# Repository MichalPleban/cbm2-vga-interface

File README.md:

# VGA interface for Commodore CBM-II computers

This project adds a VGA interface to Commodore CBM-II machines. The board can be installed in both low-profile and high-profile machines and adds a VGA connector which mirrors the main display.

## Project aims

This is a VGA **interface**, not a VGA **graphics card**. It does not add any graphical capabilities to your computer besides those it already possesses. What it does is to allow you to connect your computer to a modern VGA display (or a VGA-to-HDMI converter), giving you a better quality picture than a composite video output.

Due to the nature of its operation (explained below), it will also allow you to check the operation of your computer if you don't get any display from it. Since it does not depend on the inbuilt video circuitry, you can check if the CPU is booting even if the primary display is not working.

## Project status

The hardware part is ready. You can find the PCB files from the `eagle` directory. There are two PCBs: main board (to be installed in an expansion socket on the mainboard) and connector board (to be installed, for example, on the metal backplate). The boards are connected via a 2x5 pin header cable (for example, a JTAG cable).

The firmware is not yet completed but it is usable enough. It displays the picture, allows for cursor positioning and switching between text and graphics mode. These features are enough to use your computer. Advanced CRTC functions (such as changing the cursor shape) are not yet supported. You can find the current firmware binary in the `firmware` directory. You need to program the onboard 24C256 EEPROM chip with the firmware.

## How it works?

The board is centered around a Propeller v1 chip which generates a 640x480 VGA video signal. The chip is programmed to silently sniff signals on the 6509 CPU bus and react to writes to the I/O area. Through this it maintains its own copy of the video memory as well as the CRTC and TPI registers, which allows it to re-create the screen contents and display it on the VGA connector.

This way the board does not need any changes in the KERNAL video routines. Also, since it doesn't use the original video signal in ay way, you can use the board even if the primary video circuitry of the computer is not working.

## Advanced stuff

The board is also meant to be used with the 8088 board. To that end it provides a second display mode which is compatible with IBM MDA display. This mode uses an IBM 8x16 font and recognizes all MDA attributes (bright, invert, underline, blink).

There is a second connector on the board labeled `INPUT`. It is meant for daisy-chaining a secondary video board [when it is developed :)]. When a secondary board is connected, the video outputs of the primary board are tristated. This way the two cards can share the same VGA output connector.

The Propeller emits a 50 Hz signal on one of the pins. This signal is very useful if you want to replace the original power supply with a modern one. Besides various voltages, the original PSU supplies a 50 Hz signal, which modern PSUs do not. You can now easily overcome this problem by shorting the JP2 jumper on the VGA interface which will then provide the needed 50 Hz signal to the mainboard.

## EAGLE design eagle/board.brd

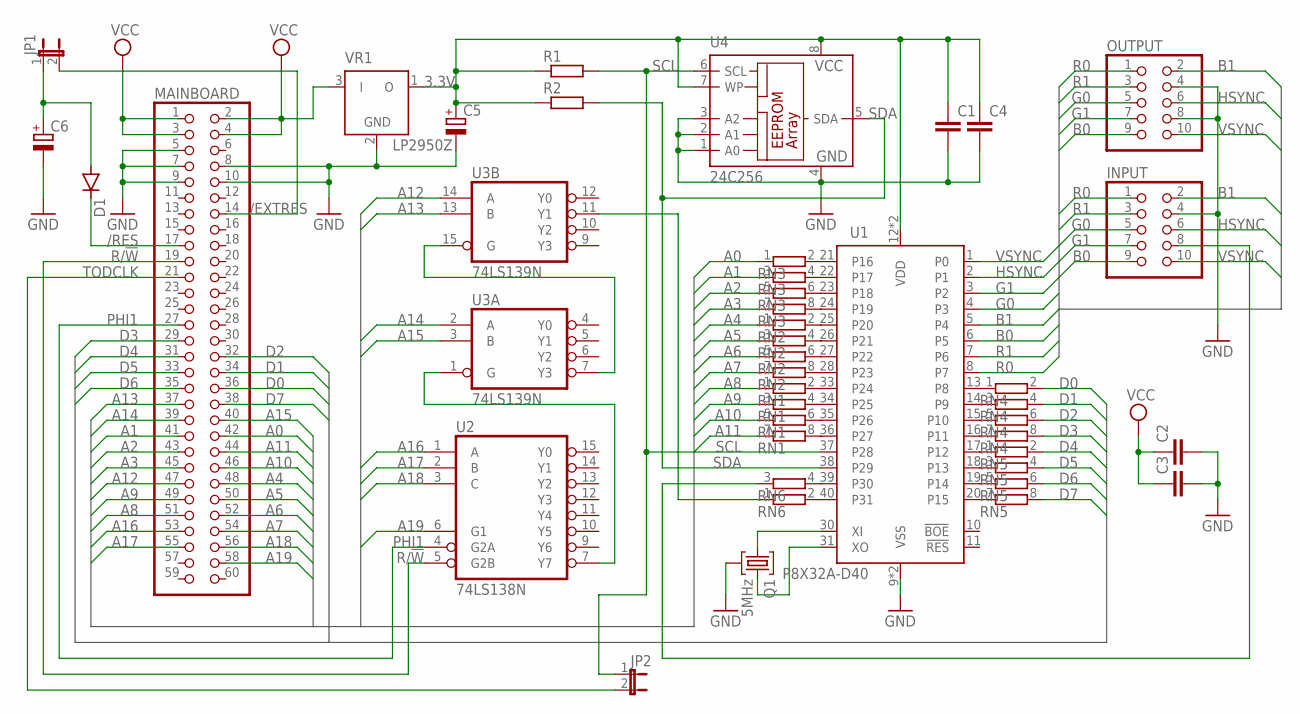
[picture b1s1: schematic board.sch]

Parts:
C1, C2, C3, C4: C2.5/2; C2.5-2
C5, C6: CPOL-EUE5-6; E5-6
D1: 1N4148DO35-7; DO35-7
INPUT: PINHD-2X5; 2X05
JP1, JP2: JP1E; JP1
MAINBOARD: PINHD-2X30; 2X30
OUTPUT: PINHD-2X5; 2X05
Q1: 5MHz; UM1
R1, R2: R-EU_0204/7; 0204/7
RN1, RN2, RN3, RN4, RN5, RN6: E4RP; SIL8
U1: P8X32A-D40; DIL40
U2: 74LS138N; DIL16
U3: 74LS139N; DIL16
U4: 24C256; DIL8
VR1: LP2950Z; TO92

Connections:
3.3V: C1.1, C4.1, C5.+, R1.1, R2.1, U1.12 (VDD), U1.32 (VDD), U4.7 (WP), U4.8 (VCC), VR1.1 (O)
/EXTRES: JP1.2, MAINBOARD.14
/RES: D1.C, MAINBOARD.17
A0: MAINBOARD.42, RN3.1
A1: MAINBOARD.41, RN3.3 (1)
A2: MAINBOARD.43, RN3.5 (1)
A3: MAINBOARD.45, RN3.7 (1)
A4: MAINBOARD.48, RN2.1
A5: MAINBOARD.50, RN2.3 (1)
A6: MAINBOARD.52, RN2.5 (1)
A7: MAINBOARD.54, RN2.7 (1)
A8: MAINBOARD.51, RN1.1
A9: MAINBOARD.49, RN1.3 (1)
A10: MAINBOARD.46, RN1.5 (1)
A11: MAINBOARD.44, RN1.7 (1)
A12: MAINBOARD.47, U3.14 (A)
A13: MAINBOARD.37, U3.13 (B)
A14: MAINBOARD.39, U3.2 (A)
A15: MAINBOARD.40, U3.3 (B)
A16: MAINBOARD.53, U2.1 (A)
A17: MAINBOARD.55, U2.2 (B)
A18: MAINBOARD.56, U2.3 (C)
A19: MAINBOARD.58, U2.6 (G1)
B0: INPUT.9, OUTPUT.9, U1.6 (P5)
B1: INPUT.2, OUTPUT.2, U1.5 (P4)
D0: MAINBOARD.36, RN4.2
D1: MAINBOARD.34, RN4.4 (2)
D2: MAINBOARD.32, RN4.6 (2)
D3: MAINBOARD.29, RN4.8 (2)
D4: MAINBOARD.31, RN5.2
D5: MAINBOARD.33, RN5.4 (2)
D6: MAINBOARD.35, RN5.6 (2)
D7: MAINBOARD.38, RN5.8 (2)
G0: INPUT.5, OUTPUT.5, U1.4 (P3)
G1: INPUT.7, OUTPUT.7, U1.3 (P2)
GND: C1.2, C2.2, C3.2, C4.2, C5.-, C6.-, INPUT.4, MAINBOARD.5, MAINBOARD.7, MAINBOARD.8, MAINBOARD.9, MAINBOARD.10, OUTPUT.4, OUTPUT.8, Q1.2, U1.9 (VSS), U1.29 (VSS), U2.8 (GND), U3.8 (GND), U4.1 (A0), U4.2 (A1), U4.3 (A2), U4.4 (GND), VR1.2 (GND)
HSYNC: INPUT.6, OUTPUT.6, U1.2 (P1)
unnamed: U2.7 (Y7), U3.1 (G)
unnamed: U3.7 (Y3), U3.15 (G)
unnamed: RN6.1, U3.11 (Y1)
unnamed: RN1.8 (2), U1.36 (P27)
unnamed: RN1.6 (2), U1.35 (P26)
unnamed: RN1.4 (2), U1.34 (P25)
unnamed: RN1.2, U1.33 (P24)
unnamed: RN2.8 (2), U1.28 (P23)
unnamed: RN2.6 (2), U1.27 (P22)
unnamed: RN2.4 (2), U1.26 (P21)
unnamed: RN2.2, U1.25 (P20)
unnamed: RN3.8 (2), U1.24 (P19)
unnamed: RN3.6 (2), U1.23 (P18)
unnamed: RN3.4 (2), U1.22 (P17)
unnamed: RN3.2, U1.21 (P16)
unnamed: RN5.7 (1), U1.20 (P15)
unnamed: RN5.5 (1), U1.19 (P14)
unnamed: RN5.3 (1), U1.18 (P13)
unnamed: RN5.1, U1.17 (P12)
unnamed: RN4.7 (1), U1.16 (P11)
unnamed: RN4.5 (1), U1.15 (P10)
unnamed: RN4.3 (1), U1.14 (P9)
unnamed: RN4.1, U1.13 (P8)
unnamed: RN6.2, U1.40 (P31)
unnamed: RN6.4 (2), U1.39 (P30)
unnamed: Q1.1, U1.30 (XI)
unnamed: Q1.3, U1.31 (XO)
unnamed: C6.+, D1.A, JP1.1
unnamed: INPUT.8, RN6.3 (1)
PHI1: MAINBOARD.27, U2.4 (G2A)
R0: INPUT.1, OUTPUT.1, U1.8 (P7)
R1: INPUT.3, OUTPUT.3, U1.7 (P6)
R/!W: MAINBOARD.19, U2.5 (G2B)
SCL: JP2.1, R1.2, U1.37 (P28), U4.6 (SCL)
SDA: R2.2, U1.38 (P29), U4.5 (SDA)
TODCLK: JP2.2, MAINBOARD.21
VCC: C2.1, C3.1, MAINBOARD.1, MAINBOARD.2, MAINBOARD.3, MAINBOARD.4, U2.16 (VCC), U3.16 (VCC), VR1.3 (I)
VSYNC: INPUT.10, OUTPUT.10, U1.1 (P0)

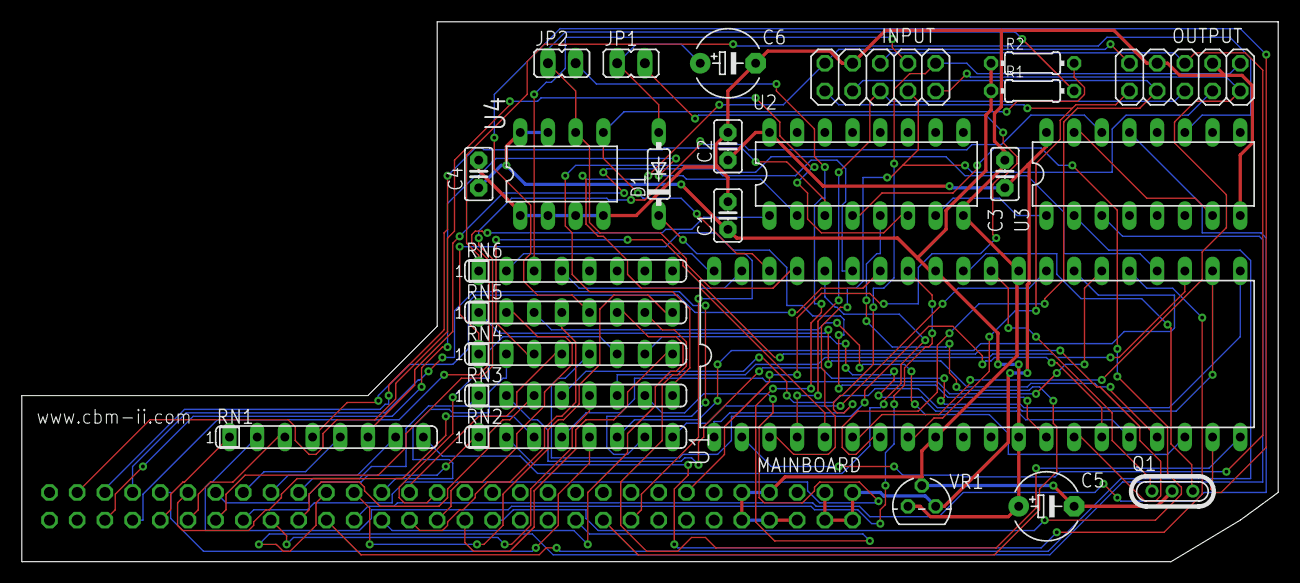
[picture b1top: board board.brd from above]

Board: 2 copper layers, 115.2 x 49.5 mm, 26 parts (1 on the bottom side), 75 nets.

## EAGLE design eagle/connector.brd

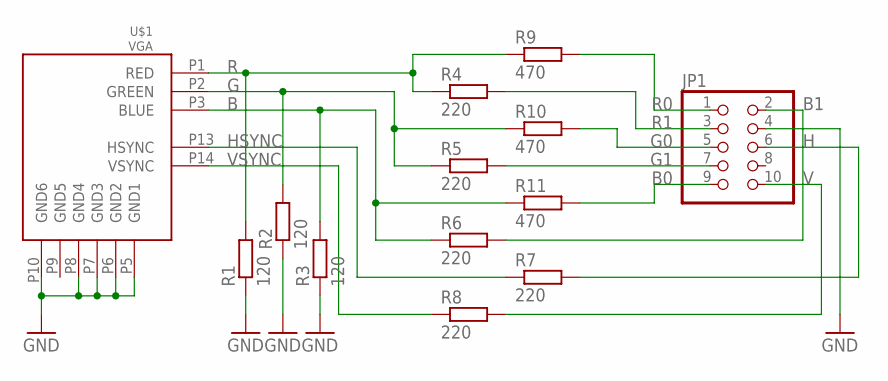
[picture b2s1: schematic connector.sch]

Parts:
JP1: PINHD-2X5; 2X05
R1, R2, R3: 120; 0204/7
R4, R5, R6, R7, R8: 220; 0204/7
R9, R10, R11: 470; 0204/7
U$1: VGA; FCI_DSUB_HD_15_RA

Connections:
B: R3.2, R6.1, R11.1, U$1.P3 (BLUE)
B0: JP1.9, R11.2
B1: JP1.2, R6.2
G: R2.2, R5.1, R10.1, U$1.P2 (GREEN)
G0: JP1.5, R10.2
G1: JP1.7, R5.2
GND: JP1.4, R1.1, R2.1, R3.1, U$1.P5 (GND1), U$1.P6 (GND2), U$1.P7 (GND3), U$1.P8 (GND4), U$1.P10 (GND6)
H: JP1.6, R7.2
HSYNC: R7.1, U$1.P13 (HSYNC)
R: R1.2, R4.1, R9.1, U$1.P1 (RED)
R0: JP1.1, R9.2
R1: JP1.3, R4.2
V: JP1.10, R8.2
VSYNC: R8.1, U$1.P14 (VSYNC)

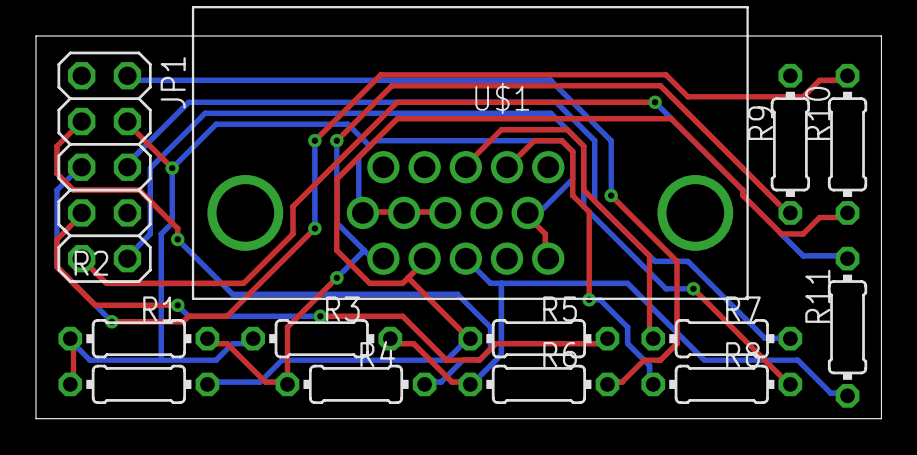
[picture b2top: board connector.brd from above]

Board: 2 copper layers, 47.0 x 21.3 mm, 13 parts (0 on the bottom side), 14 nets.

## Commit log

2021-05-21 Initial release
2021-05-22 8088 card mode
2021-05-23 Scrolling correction.
2021-05-30 MDA attribute correction.
2021-06-02 Cursor on/off
2021-06-05 Board and firmware fixes.
2021-06-21 Eliminate the color buffer
2021-06-21 Unified config array
2021-06-24 Alternate font on/off
2021-09-25 Video inverse
2021-09-25 Splash screen
2022-12-03 60Hz timer
